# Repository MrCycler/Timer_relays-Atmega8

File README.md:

# Timer_relays
Proyecto de temporización de reles configurada por el usuario basado en ATMEGA8.

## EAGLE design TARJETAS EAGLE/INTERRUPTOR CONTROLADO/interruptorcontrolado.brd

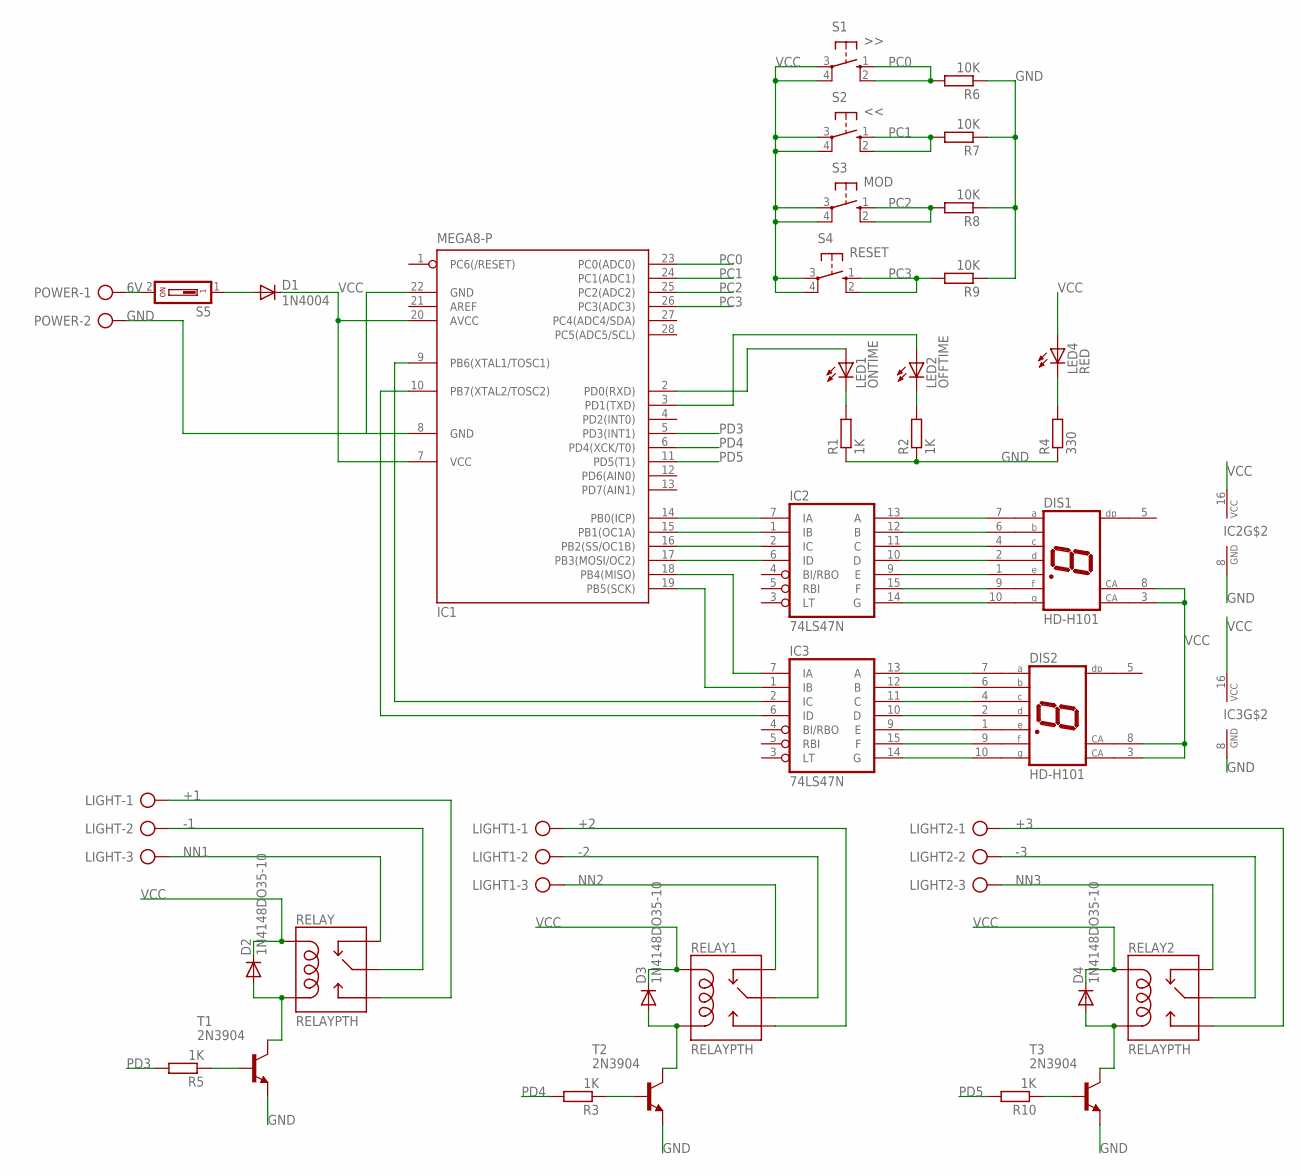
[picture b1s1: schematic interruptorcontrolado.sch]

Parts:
D1: 1N4004; DO41-10
D2, D3, D4: 1N4148DO35-10; DO35-10
DIS1, DIS2: HD-H101; HDSP-M
IC1: MEGA8-P; DIL28-3
IC2, IC3: 74LS47N; DIL16
LED1: ONTIME; LED5MM
LED2: OFFTIME; LED5MM
LED4: RED; LED5MM
LIGHT, LIGHT1, LIGHT2: AK500/3
POWER: AK500/2
R1, R2, R3, R5, R10: 1K; 0207/10
R4: 330; 0207/10
R6, R7, R8, R9: 10K; 0207/10
RELAY, RELAY1, RELAY2: RELAYPTH; SRD-05VDC-SL-C
S1: >>; B3F-10XX
S2: <<; B3F-10XX
S3: MOD; B3F-10XX
S4: RESET; B3F-10XX
S5: SD4-01
T1, T2, T3: 2N3904; TO92

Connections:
6V: POWER.1, S5.2
+1: LIGHT.1, RELAY.SWOPEN
+2: LIGHT1.1, RELAY1.SWOPEN
+3: LIGHT2.1, RELAY2.SWOPEN
-1: LIGHT.2, RELAY.SWCOMMON
-2: LIGHT1.2, RELAY1.SWCOMMON
-3: LIGHT2.2, RELAY2.SWCOMMON
GND: IC1.8 (GND), IC1.22 (GND), IC2.8 (GND), IC3.8 (GND), POWER.2, R1.1, R2.1, R4.1, R6.1, R7.1, R8.1, R9.1, T1.3 (E), T2.3 (E), T3.3 (E)
unnamed: IC1.14 (PB0(ICP)), IC2.7 (IA)
unnamed: IC1.15 (PB1(OC1A)), IC2.1 (IB)
unnamed: IC1.16 (PB2(SS/OC1B)), IC2.2 (IC)
unnamed: IC1.17 (PB3(MOSI/OC2)), IC2.6 (ID)
unnamed: IC1.18 (PB4(MISO)), IC3.7 (IA)
unnamed: IC1.19 (PB5(SCK)), IC3.1 (IB)
unnamed: IC1.9 (PB6(XTAL1/TOSC1)), IC3.2 (IC)
unnamed: IC1.10 (PB7(XTAL2/TOSC2)), IC3.6 (ID)
unnamed: DIS1.7 (A), IC2.13 (A)
unnamed: DIS1.6 (B), IC2.12 (B)
unnamed: DIS1.4 (C), IC2.11 (C)
unnamed: DIS1.2 (D), IC2.10 (D)
unnamed: DIS1.1 (E), IC2.9 (E)
unnamed: DIS1.9 (F), IC2.15 (F)
unnamed: DIS1.10 (G), IC2.14 (G)
unnamed: DIS2.7 (A), IC3.13 (A)
unnamed: DIS2.6 (B), IC3.12 (B)
unnamed: DIS2.4 (C), IC3.11 (C)
unnamed: DIS2.2 (D), IC3.10 (D)
unnamed: DIS2.1 (E), IC3.9 (E)
unnamed: DIS2.9 (F), IC3.15 (F)
unnamed: DIS2.10 (G), IC3.14 (G)
unnamed: LED1.K (C), R1.2
unnamed: LED2.K (C), R2.2
unnamed: R3.1, T2.2 (B)
unnamed: LED4.K (C), R4.2
unnamed: IC1.2 (PD0(RXD)), LED1.A
unnamed: IC1.3 (PD1(TXD)), LED2.A
unnamed: D3.A, RELAY1.COIL0, T2.1 (C)
unnamed: R5.1, T1.2 (B)
unnamed: D2.A, RELAY.COIL0, T1.1 (C)
unnamed: R10.1, T3.2 (B)
unnamed: D1.A, S5.1
unnamed: D4.A, RELAY2.COIL0, T3.1 (C)
NN1: LIGHT.3, RELAY.SWCLOSED (SWCLOSE)
NN2: LIGHT1.3, RELAY1.SWCLOSED (SWCLOSE)
NN3: LIGHT2.3, RELAY2.SWCLOSED (SWCLOSE)
PC0: IC1.23 (PC0(ADC0)), R6.2, S1.1 (S), S1.2 (S1)
PC1: IC1.24 (PC1(ADC1)), R7.2, S2.1 (S), S2.2 (S1)
PC2: IC1.25 (PC2(ADC2)), R8.2, S3.1 (S), S3.2 (S1)
PC3: IC1.26 (PC3(ADC3)), R9.2, S4.1 (S), S4.2 (S1)
PD3: IC1.5 (PD3(INT1)), R5.2
PD4: IC1.6 (PD4(XCK/T0)), R3.2
PD5: IC1.11 (PD5(T1)), R10.2
VCC: D1.C, D2.C, D3.C, D4.C, DIS1.3 (CA), DIS1.8 (CA), DIS2.3 (CA), DIS2.8 (CA), IC1.7 (VCC), IC1.20 (AVCC), IC2.16 (VCC), IC3.16 (VCC), LED4.A, RELAY.COIL1, RELAY1.COIL1, RELAY2.COIL1, S1.3, S1.4 (P1), S2.3, S2.4 (P1), S3.3, S3.4 (P1), S4.3, S4.4 (P1)

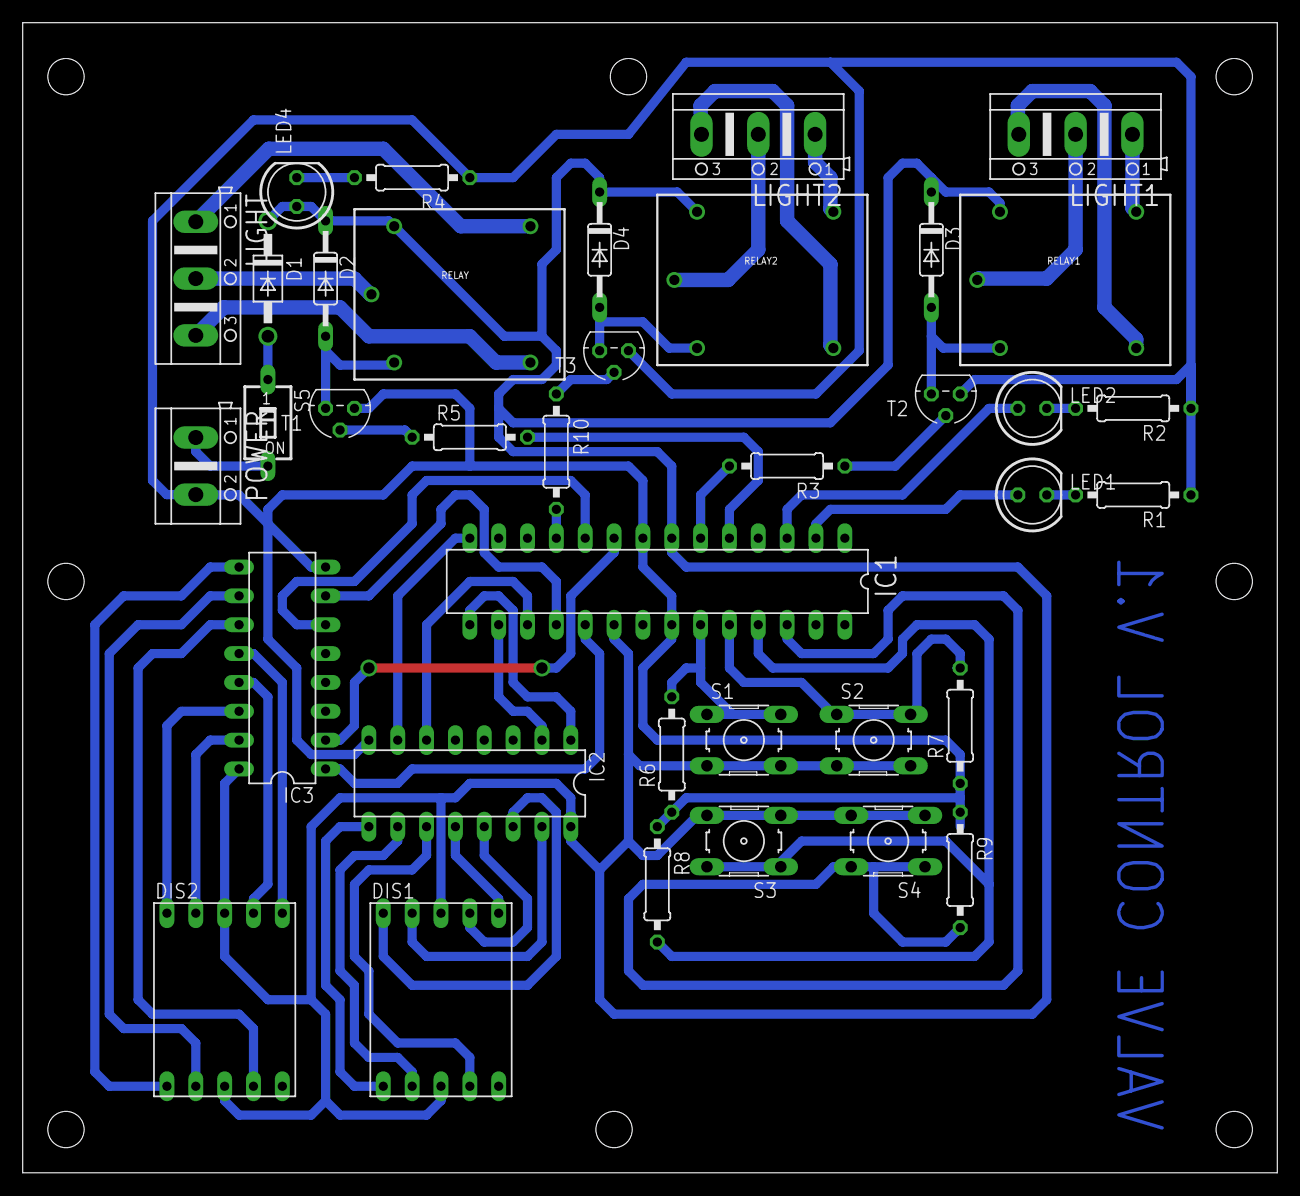
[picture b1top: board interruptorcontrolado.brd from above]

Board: 2 copper layers, 110.5 x 101.3 mm, 37 parts (0 on the bottom side), 53 nets.

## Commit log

2017-12-01 Proyecto completo documentado
